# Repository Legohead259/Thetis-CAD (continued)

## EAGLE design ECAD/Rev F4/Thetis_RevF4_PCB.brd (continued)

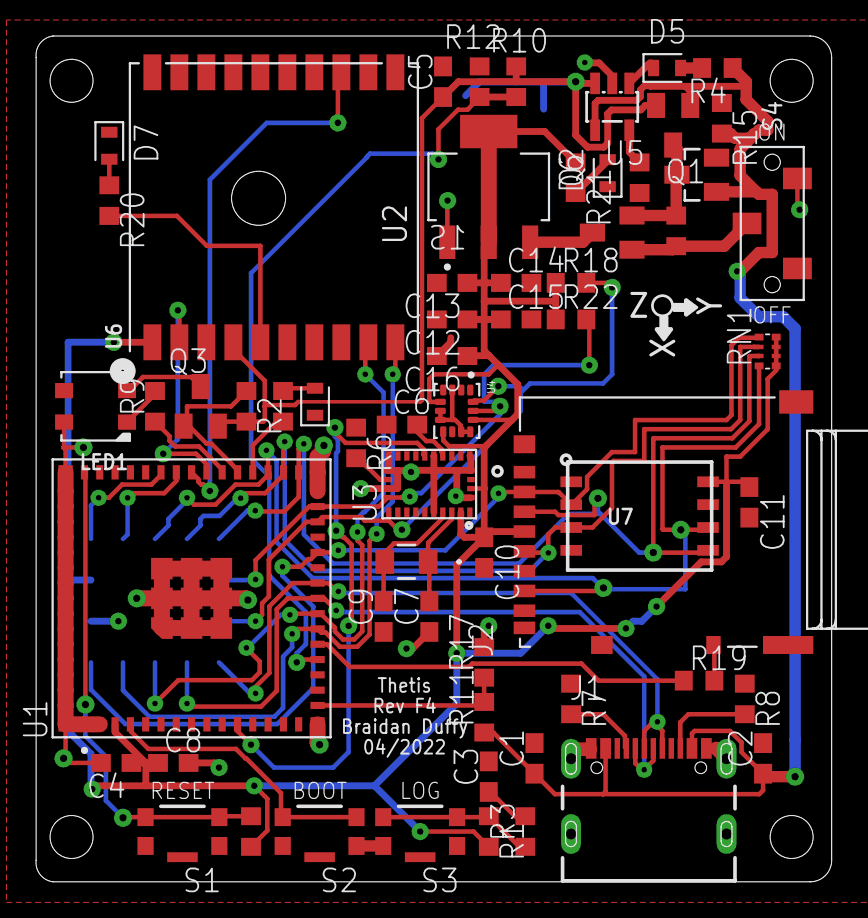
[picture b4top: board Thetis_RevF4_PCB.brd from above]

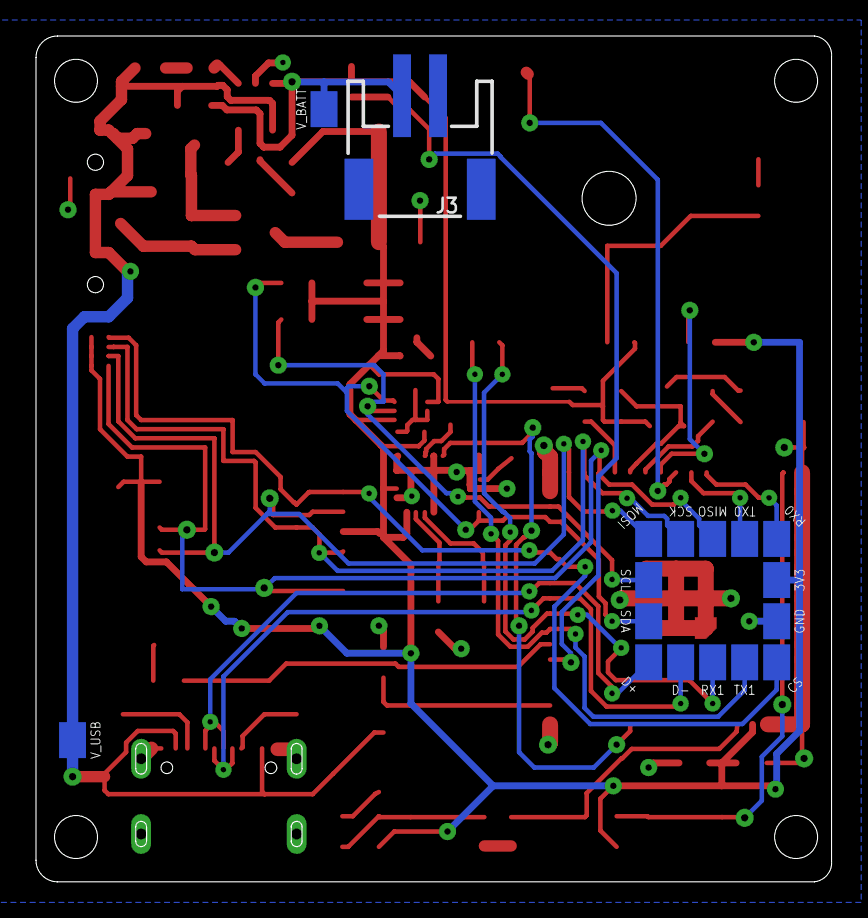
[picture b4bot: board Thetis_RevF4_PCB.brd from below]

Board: 2 copper layers, 44.2 x 47.0 mm, 79 parts (17 on the bottom side), 48 nets.

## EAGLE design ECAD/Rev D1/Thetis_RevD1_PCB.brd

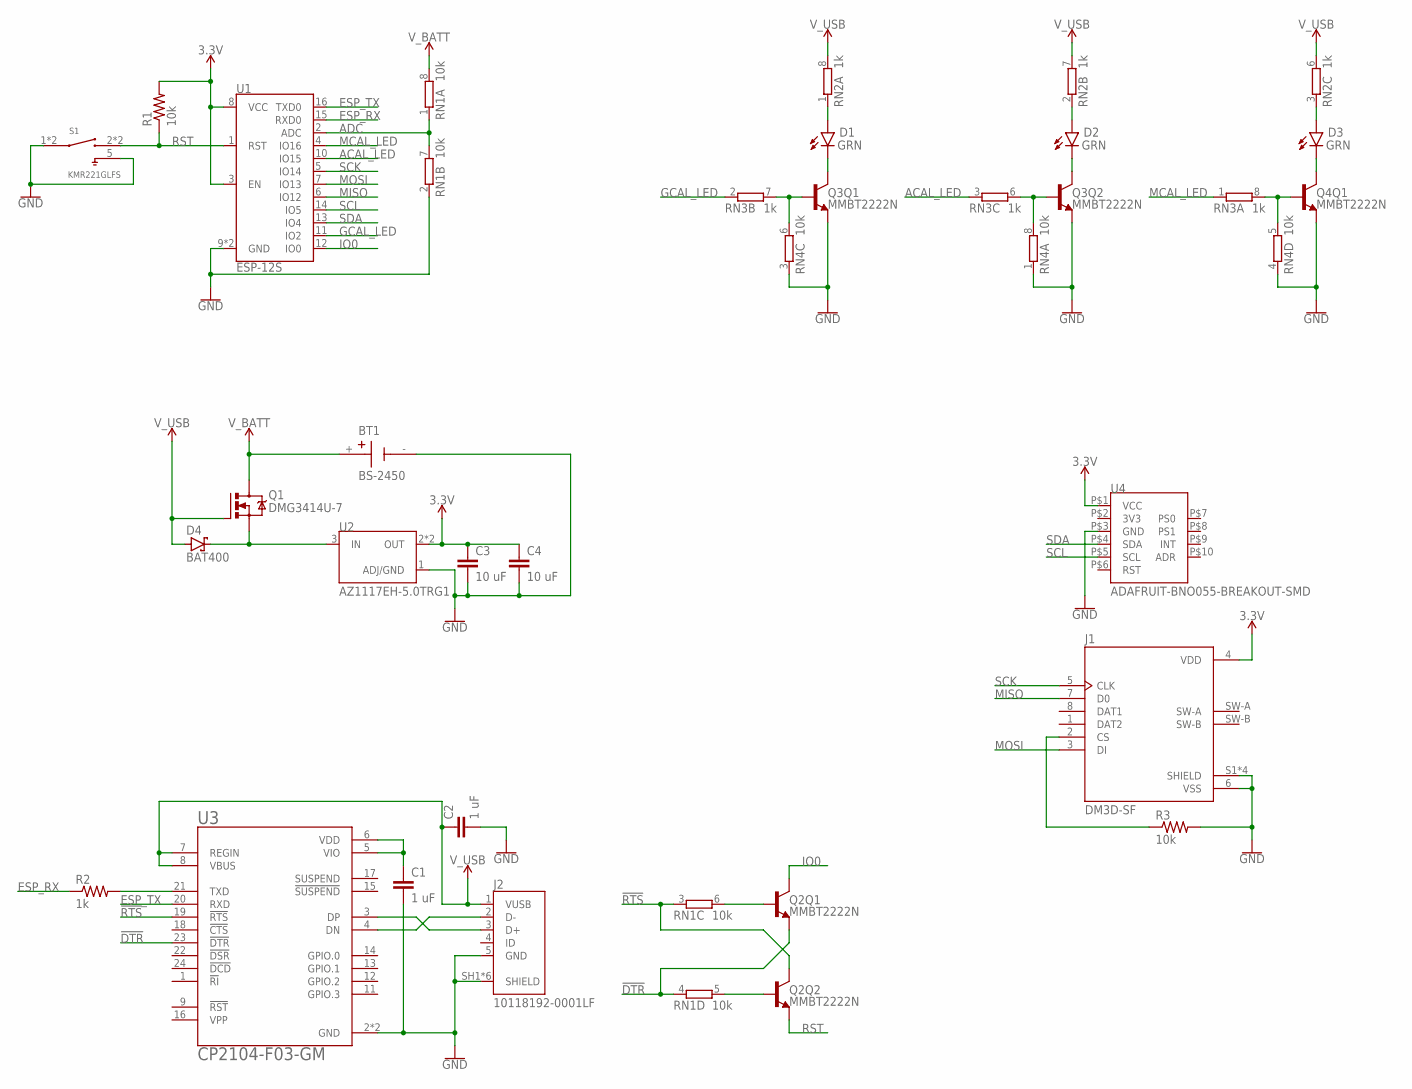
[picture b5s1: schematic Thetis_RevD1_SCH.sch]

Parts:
BT1: BS-2450; BAT_BS-2450
C1, C2: 1 uF; C0603
C3, C4: 10 uF; C0603
D1, D2, D3: GRN; LEDC1608X65N
D4: BAT400; SOT23
J1: DM3D-SF; HRS_DM3D-SF
J2: 10118192-0001LF; AMPHENOL_10118192-0001LF
Q1: DMG3414U-7; SOT23
Q2, Q3, Q4: MMBT2222N; SC70-6
R1, R3: 10k; R0603
R2: 1k; R0603
RN1, RN4: 10k; EXB28V
RN2, RN3: 1k; EXB28V
S1: KMR221GLFS; SW_KMR221GLFS
U1: ESP-12S
U2: AZ1117EH-5.0TRG1; SOT230P700X180-4N
U3: CP2104-F03-GM; QFN50P400X400X80-25N
U4: ADAFRUIT-BNO055-BREAKOUT-SMD

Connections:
3.3V: C3.1, C4.1, J1.4 (VDD), R1.2, U1.3 (EN), U1.8 (VCC), U2.2 (OUT), U2.4 (OUT), U4.P$1 (VCC)
3V3: U4.P$2 (3V3)
!DTR: Q2.4 (E), RN1.4 (1), U3.23 (!DTR)
!RTS: Q2.6 (C), RN1.3 (1), U3.19 (!RTS)
ACAL_LED: RN3.3 (1), U1.10 (IO15)
ADC: RN1.1, RN1.7 (2), U1.2 (ADC)
ESP_RX: R2.1, U1.15 (RXD0)
ESP_TX: U1.16 (TXD0), U3.20 (RXD)
GCAL_LED: RN3.2 (1), U1.11 (IO2)
GND: BT1.-, C1.2, C2.2, C3.2, C4.2, J1.6 (VSS), J1.S1 (SHIELD), J1.S2 (SHIELD), J1.S3 (SHIELD), J1.S4 (SHIELD), J2.5 (GND), J2.SH1 (SHIELD), J2.SH2 (SHIELD), J2.SH3 (SHIELD), J2.SH4 (SHIELD), J2.SH5 (SHIELD), J2.SH6 (SHIELD), Q3.1 (E), Q3.4 (E), Q4.4 (E), R3.2, RN1.2 (1), RN4.1, RN4.3 (1), RN4.4 (1), S1.1, S1.4 (1), S1.5, U1.9 (GND), U1.P$1 (GND), U2.1 (ADJ/GND), U3.2 (GND), U3.25 (GND), U4.P$3 (GND)
IO0: Q2.3 (C), U1.12 (IO0)
MCAL_LED: RN3.1, U1.4 (IO16)
MISO: J1.7 (D0), U1.6 (IO12)
MOSI: J1.3 (DI), U1.7 (IO13)
unnamed: J1.2 (CS), R3.1
unnamed: C1.1, U3.5 (VIO), U3.6 (VDD)
unnamed: R2.2, U3.21 (TXD)
unnamed: J2.3 (D+), U3.3 (DP)
unnamed: J2.2 (D-), U3.4 (DN)
unnamed: Q3.5 (B), RN3.7 (2), RN4.6 (2)
unnamed: Q2.2 (B), RN1.5 (2)
unnamed: D1.C, Q3.3 (C)
unnamed: Q2.5 (B), RN1.6 (2)
unnamed: D1.A, RN2.1
unnamed: D2.A, RN2.2 (1)
unnamed: D2.C, Q3.6 (C)
unnamed: D4.3 (C), Q1.2 (S), U2.3 (IN)
unnamed: Q3.2 (B), RN3.6 (2), RN4.8 (2)
unnamed: Q4.5 (B), RN3.8 (2), RN4.5 (2)
unnamed: D3.C, Q4.3 (C)
unnamed: D3.A, RN2.3 (1)
RST: Q2.1 (E), R1.1, S1.2 (3), S1.3, U1.1 (RST)
SCK: J1.5 (CLK), U1.5 (IO14)
SCL: U1.14 (IO5), U4.P$5 (SCL)
SDA: U1.13 (IO4), U4.P$4 (SDA)
V_BATT: BT1.+, Q1.3 (D), RN1.8 (2)
V_USB: C2.1, D4.1 (A), J2.1 (VUSB), Q1.1 (G), RN2.6 (2), RN2.7 (2), RN2.8 (2), U3.7 (REGIN), U3.8 (VBUS)

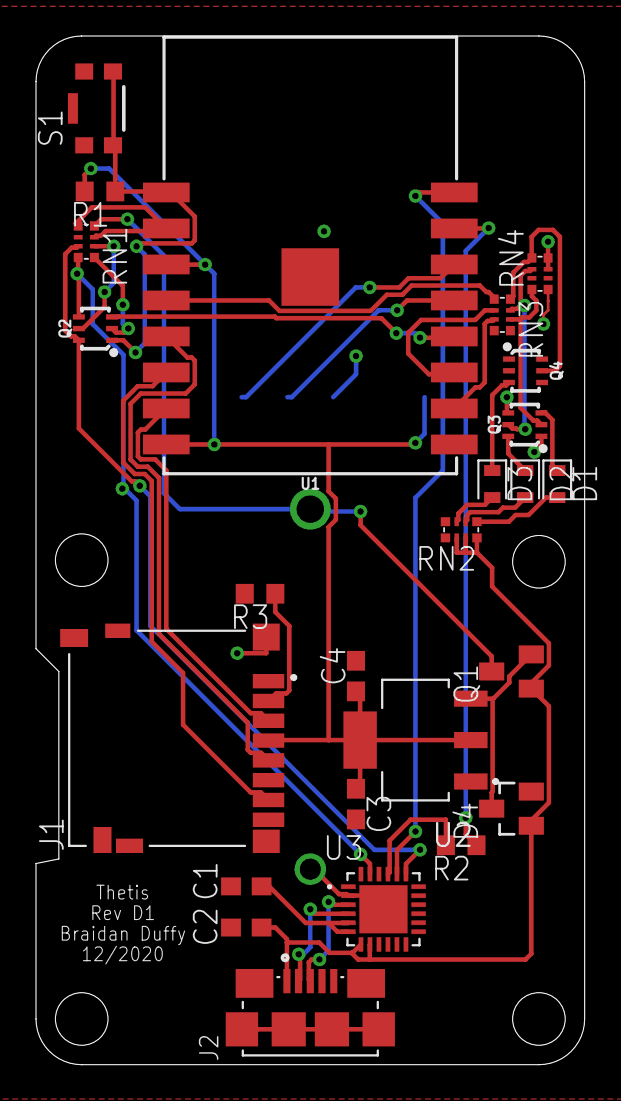
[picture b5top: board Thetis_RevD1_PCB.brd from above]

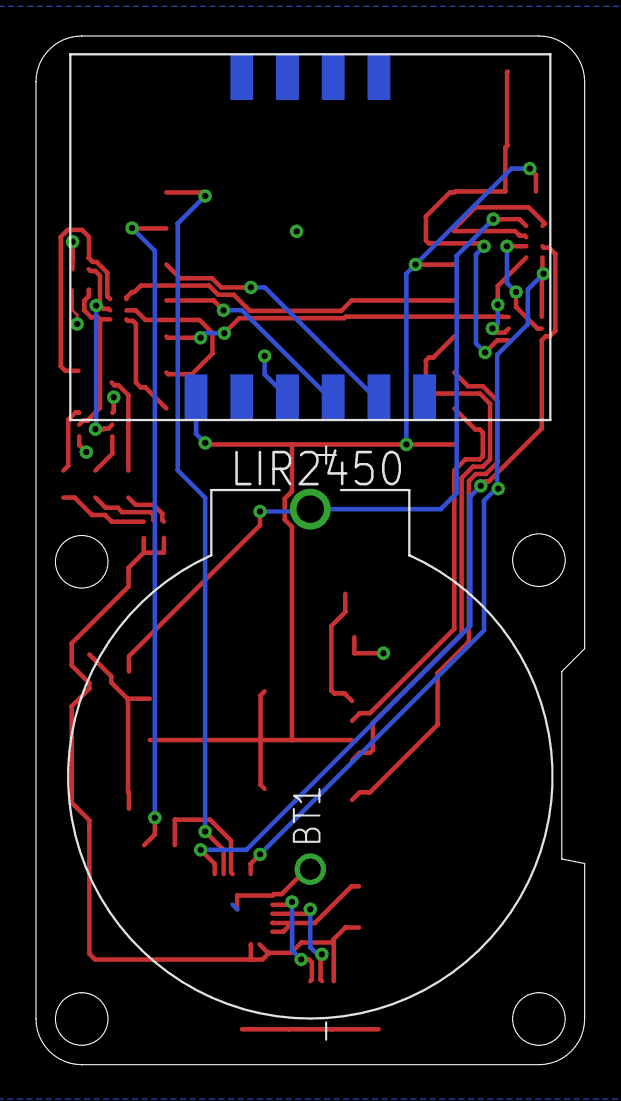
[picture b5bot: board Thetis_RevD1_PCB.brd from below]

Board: 2 copper layers, 30.5 x 57.1 mm, 27 parts (2 on the bottom side), 36 nets.

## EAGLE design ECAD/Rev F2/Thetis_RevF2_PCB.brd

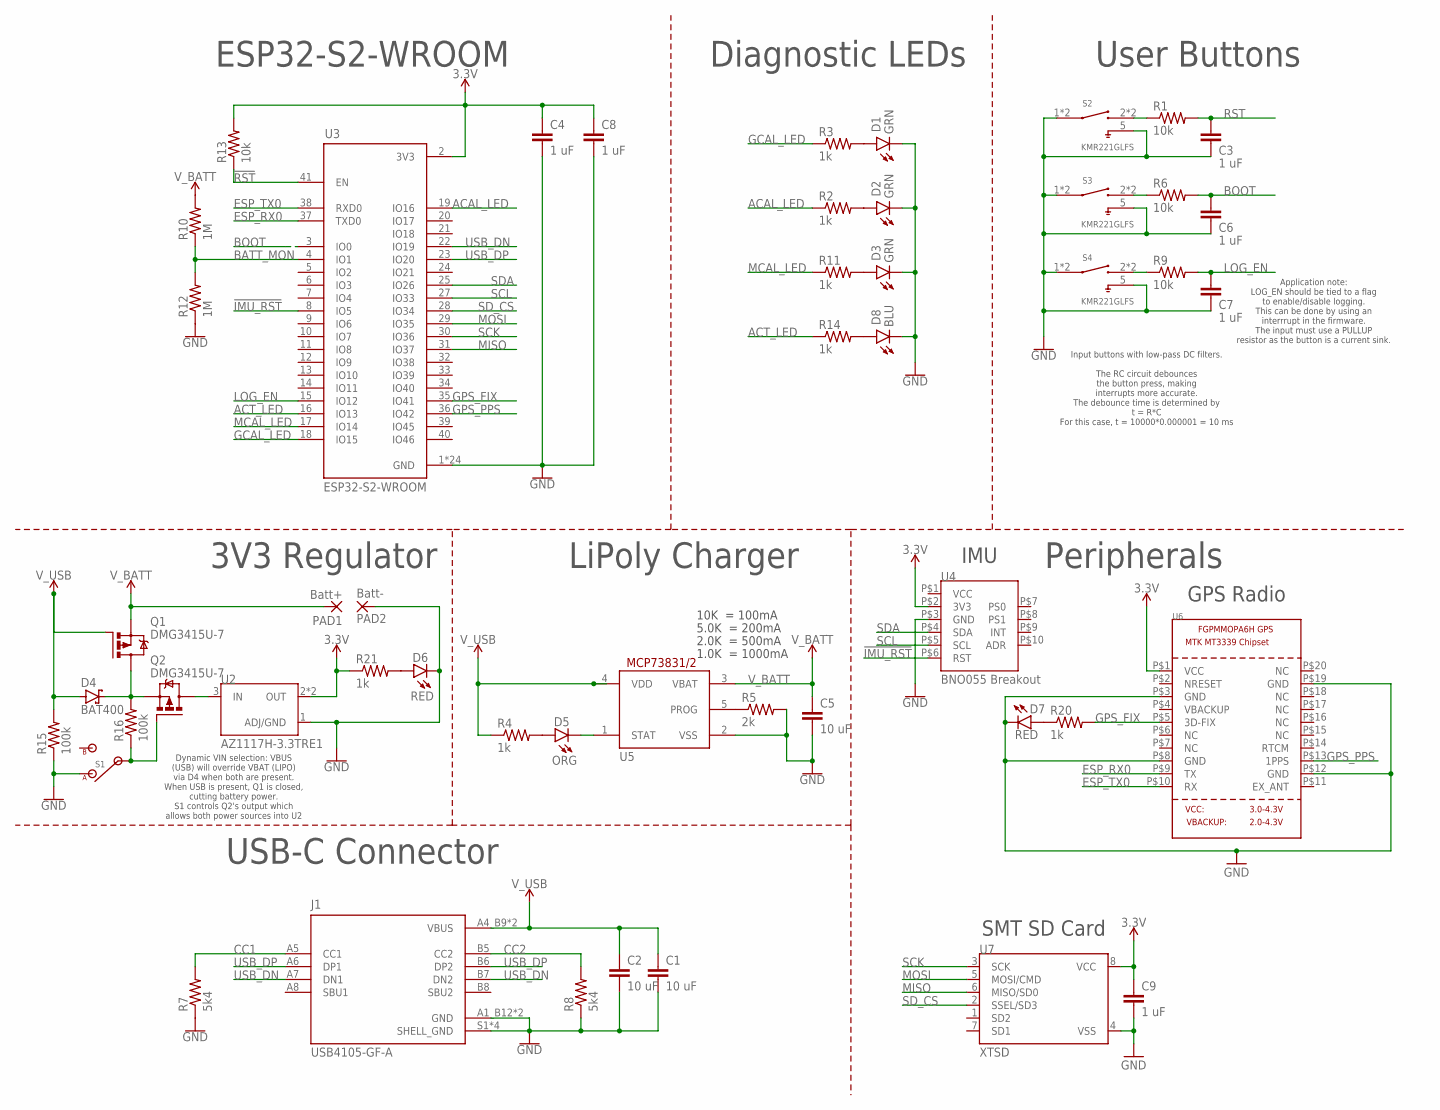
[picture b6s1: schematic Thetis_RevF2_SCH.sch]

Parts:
C1, C2, C5: 10 uF; C0603
C3, C4, C6, C7, C8, C9: 1 uF; C0603
D1, D2, D3: GRN; LEDC1608X65N
D4: BAT400; SOT23
D5: ORG; LEDC1608X65N
D6: RED; LEDC1608X65N
D7: RED; LEDC1608X35N
D8: BLU; LEDC1608X65N
J1: USB4105-GF-A; GCT_USB4105-GF-A
PAD1: Batt+; SMD2,54-5,08
PAD2: Batt-; SMD2,54-5,08
Q1, Q2: DMG3415U-7; SOT23
R1, R6, R9, R13: 10k; R0603
R2, R3, R4, R11, R14, R20, R21: 1k; R0603
R5: 2k; R0603
R7, R8: 5k4; R0603
R10, R12: 1M; R0603
R15, R16: 100k; R0603
S1: CL-SB-12X; CL-SB-12A
S2, S3, S4: KMR221GLFS; SW_KMR221GLFS
U2: AZ1117H-3.3TRE1; SOT230P700X180-4N
U3: ESP32-S2-WROOM; XCVR_ESP32-S2-WROOM
U4: BNO055 Breakout; ADAFRUIT-BNO055-BREAKOUT-SMD
U5: MCP73831/OT; SOT23-5L
U6: GPS_FGPMMOPA6H; FGPMMOPA6H
U7: XTSD; LGA8_8X6

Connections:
3.3V: C4.1, C8.1, C9.1, R13.2, R21.1, U2.2 (OUT), U2.4 (OUT), U3.2 (3V3), U4.P$2 (3V3), U6.P$1 (VCC), U7.8 (VCC)
!IMU_RST: U3.8 (IO5), U4.P$6 (RST)
!RST: R13.1, U3.41 (EN)
ACAL_LED: R2.1, U3.19 (IO16)
ACT_LED: R14.1, U3.16 (IO13)
BATT_MON: R10.1, R12.2, U3.4 (IO1)
BOOT: C6.1, R6.2, U3.3 (IO0)
CC1: J1.A5 (CC1), R7.2
CC2: J1.B5 (CC2), R8.2
ESP_RX0: U3.37 (TXD0), U6.P$9 (TX)
ESP_TX0: U3.38 (RXD0), U6.P$10 (RX)
GCAL_LED: R3.1, U3.18 (IO15)
GND: C1.2, C2.2, C3.2, C4.2, C5.2, C6.2, C7.2, C8.2, C9.2, D1.C, D2.C, D3.C, D6.C, D7.C, D8.C, J1.A1_B12 (GND), J1.B1_A12 (GND), J1.S1 (SHELL_GND), J1.S2 (SHELL_GND), J1.S3 (SHELL_GND), J1.S4 (SHELL_GND), PAD2.1, R5.2, R7.1, R8.1, R12.1, R15.1, S1.1, S2.1, S2.4 (1), S2.5, S3.1, S3.4 (1), S3.5, S4.1, S4.4 (1), S4.5, U2.1 (ADJ/GND), U3.1 (GND), U3.26 (GND), U3.42 (GND), U3.43.1 (GND), U3.43.2 (GND), U3.43.3 (GND), U3.43.4 (GND), U3.43.5 (GND), U3.43.6 (GND), U3.43.7 (GND), U3.43.8 (GND), U3.43.9 (GND), U3.43.10 (GND), U3.43.11 (GND), U3.43.12 (GND), U3.43.13 (GND), U3.43.14 (GND), U3.43.15 (GND), U3.43.16 (GND), U3.43.17 (GND), U3.43.18 (GND), U3.43.19 (GND), U3.43.20 (GND), U3.43.21 (GND), U4.P$3 (GND), U5.2 (VSS), U6.P$3 (GND), U6.P$8 (GND), U6.P$12 (GND), U6.P$19 (GND), U7.4 (VSS)
GPS_FIX: R20.2, U3.35 (IO41), U6.P$5 (3D-FIX)
GPS_PPS: U3.36 (IO42), U6.P$13 (1PPS)
LOG_EN: C7.1, R9.2, U3.15 (IO12)
MCAL_LED: R11.1, U3.17 (IO14)
MISO: U3.31 (IO37), U7.6 (MISO/SD0)
MOSI: U3.29 (IO35), U7.5 (MOSI/CMD)
unnamed: D7.A, R20.1
unnamed: D8.A, R14.2
unnamed: R1.1, S2.2 (3), S2.3
unnamed: Q2.3 (D), U2.3 (IN)
unnamed: R6.1, S3.2 (3), S3.3
unnamed: D1.A, R3.2
unnamed: Q2.1 (G), R16.1, S1.2
unnamed: R9.1, S4.2 (3), S4.3
unnamed: D2.A, R2.2
unnamed: D4.3 (C), Q1.3 (D), Q2.2 (S), R16.2
unnamed: D3.A, R11.2
unnamed: D5.A, R4.2
unnamed: D5.C, U5.1 (STAT)
unnamed: R5.1, U5.5 (PROG)
unnamed: D6.A, R21.2
RST: C3.1, R1.2
SCK: U3.30 (IO36), U7.3 (SCK)
SCL: U3.27 (IO33), U4.P$5 (SCL)
SDA: U3.25 (IO26), U4.P$4 (SDA)
SD_CS: U3.28 (IO34), U7.2 (SSEL/SD3)
USB_DN: J1.A7 (DN1), J1.B7 (DN2), U3.22 (IO19)
USB_DP: J1.A6 (DP1), J1.B6 (DP2), U3.23 (IO20)
VCC: U4.P$1 (VCC)
V_BATT: C5.1, PAD1.1, Q1.2 (S), R10.2, U5.3 (VBAT)
V_USB: C1.1, C2.1, D4.1 (A), J1.A4_B9 (VBUS), J1.B4_A9 (VBUS), Q1.1 (G), R4.1, R15.2, U5.4 (VDD)

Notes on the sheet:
10K = 100mA
5.0K = 200mA
2.0K = 500mA
1.0K = 1000mA
LiPoly Charger
3V3 Regulator
Peripherals
Diagnostic LEDs
ESP32-S2-WROOM
GPS Radio
Dynamic VIN selection: VBUS (USB) will override VBAT (LIPO) via D4 when both are present. When USB is present, Q1 is closed, cutting battery power. S1 controls Q2's output which allows both power sources into U2
IMU
SMT SD Card
USB-C Connector
Input buttons with low-pass DC filters. The RC circuit debounces the button press, making interrupts more accurate. The debounce time is determined by t = R*C For this case, t = 10000*0.000001 = 10 ms
User Buttons
Application note: LOG_EN should be tied to a flag to enable/disable logging. This can be done by using an interrrupt in the firmware. The input must use a PULLUP resistor as the button is a current sink.

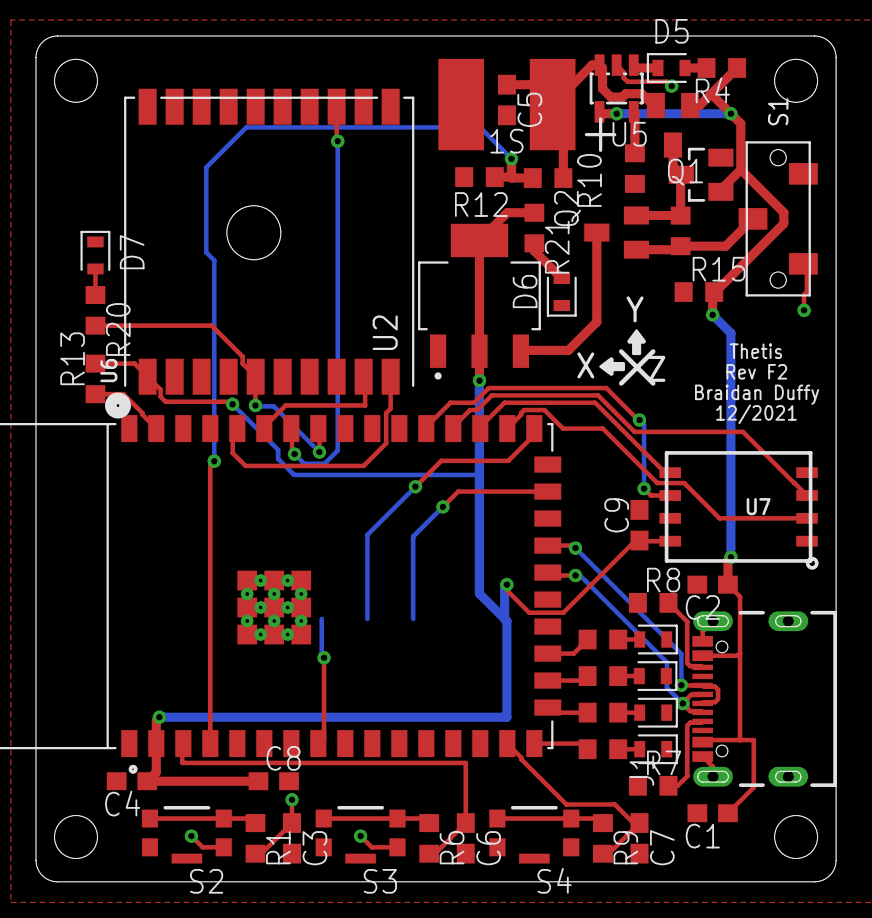
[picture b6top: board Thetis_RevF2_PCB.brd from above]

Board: 2 copper layers, 44.4 x 47.0 mm, 50 parts (1 on the bottom side), 43 nets.

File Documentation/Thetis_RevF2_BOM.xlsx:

Item | Manufactor Part Number | Supplier | Supplier Part Number | Name | Value | Package | Unit Price | Quantity | Total Price | Location | Datasheet | Notes
Battery Controller | MCP73831T-2ACI/OT | Digikey | MCP73831T-2ACI/OTCT-ND | U5 | 1S | SOT23-5 | 0.56000000000000005 | 1 | 0.56000000000000005 | https://www.digikey.com/en/products/detail/microchip-technol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 | http://www.microchip.com/mymicrochip/filehandler.aspx?ddocna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 | 1S LiPo
Button - Momentary | KMR221GLFS | Digikey | 401-1427-1-ND | S2, S3, S4 | SPST-NO | SMD | 0.49 | 3 | 1.47 | https://www.digikey.com/en/products/detail/c-k/KMR221GLFS/55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 | https://www.ckswitches.com/media/1479/kmr2.pdf | 0.05A 32V
Capacitor | 885012206026 | DigiKey | 732-7945-1-ND | C4, C8, C3, C6, C7, C9 | 1 uF | 0603 | 0.23 | 6 | 1.3800000000000001 | https://www.digikey.com/product-detail/en/wurth-electronics-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 | https://katalog.we-online.de/pbs/datasheet/885012206026.pdf | 10V X7R
Capacitor | ZRB18AR61E106ME01L | Digikey | 490-10991-1-ND | C1, C2, C5 | 10 uF | 0603 | 0.35599999999999998 | 3 | 1.0680000000000001 | https://www.digikey.com/product-detail/en/murata-electronics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 | https://search.murata.co.jp/Ceramy/image/img/A01X/G101/ENG/Z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 | 25V X5R
Connector - USB-C | USB4105-GF-A | DigiKey | 2073-USB4105-GF-ATR-ND | J1 |  | SMD | 0.72 | 1 | 0.72 | https://www.digikey.com/en/products/detail/USB4105-GF-A/2073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 | https://gct.co/files/specs/usb4105-spec.pdf | USB2.0, USB-C receptacle
Diode - Schottky | BAT400D-7-F | Digikey | BAT400D-FDICT-ND | D4 |  | SOT23-3 | 0.45 | 1 | 0.45 | https://www.digikey.com/product-detail/en/diodes-incorporate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 | https://www.diodes.com/assets/Datasheets/ds30182.pdf | 40V, 500mA
IMU | BNO055 | Adafruit | 2472 | U4 |  | SMT | 34.950000000000003 | 1 | 34.950000000000003 | https://www.adafruit.com/product/2472 | https://learn.adafruit.com/adafruit-bno055-absolute-orientat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 | Breakout board soldered to back of PCB
LED | SML-D12P8WT86C | DigiKey | SML-D12P8WT86CCT-ND | D1, D2, D3 | GRN | 0603 | 0.48 | 3 | 1.44 | https://www.digikey.com/product-detail/en/rohm-semiconductor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 | https://www.rohm.com/datasheet/SML-D12P8W(C)/sml-d12x8(c)-e | 2.2Vf
LED | 150060BS55040 | Digikey | 732-12013-1-ND | D8 | BLU | 0603 | 0.17 | 1 | 0.17 | https://www.digikey.com/product-detail/en/wurth-electronics-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 | https://katalog.we-online.de/pbs/datasheet/150060BS55040.pdf | 3.2Vf
LED | SML-D12U1WT86 | Digikey | SML-D12U1WT86CT-ND | D6, D7 | RED | 0603 | 0.16200000000000001 | 2 | 0.32400000000000001 | https://www.digikey.com/product-detail/en/rohm-semiconductor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 | https://www.rohm.com/datasheet/SML-D12U1W | 2.2Vf
LED | ASMT-RA45-AP932 | Digikey | 516-3217-1-ND | D5 | AMB | 0603 | 0.33300000000000002 | 1 | 0.33300000000000002 | https://www.digikey.com/product-detail/en/broadcom-limited/A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 | https://docs.broadcom.com/docs/AV02-0378EN | 2Vf
Microcontroller | ESP32-S2-WROOM | DigiKey | 1965-ESP32-S2-WROOMCT-ND | U3 |  | SMT | 2.13 | 1 | 2.13 | https://www.digikey.com/en/products/detail/espressif-systems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 | https://www.espressif.com/sites/default/files/documentation/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
MOSFET - P-Channel | AOSS21311C | DigiKey | 785-AOSS21311CCT-ND | Q1, Q2 |  | SOT-23-3 | 0.36199999999999999 | 2 | 0.72399999999999998 | https://www.digikey.com/en/products/detail/AOSS21311C/785-AO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 | http://aosmd.com/res/data_sheets/AOSS21311C.pdf | Vgs = -1.7V, 30V, 4.3A
Radio - GPS | PA6H | Adafruit | 790 | U6 |  | SMT | 29.95 | 1 | 29.95 | https://www.adafruit.com/product/790 |  | MTK3339 GPS
Regulator - LDO | AZ1117H-3.3TRE1 | Digikey | AZ1117H-3.3TRE1DICT-ND | U2 | 3V3 | SOT223 | 0.51 | 1 | 0.51 | https://www.digikey.com/en/products/detail/diodes-incorporat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 | https://media.digikey.com/pdf/Data%20Sheets/Diodes%20PDFs/AZ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 | LDO 1A max
Resistor | RNCP0603FTD10K0 | DigiKey | RNCP0603FTD10K0CT-ND | R13, R1, R6, R7 | 10 kΩ | 0603 | 2.7300000000000001E-2 | 4 | 0.10920000000000001 | https://www.digikey.com/product-detail/en/stackpole-electron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 | https://www.seielect.com/catalog/sei-rncp.pdf | 0.125W
Resistor | CRCW06031M00FKEAC | DigiKey | 541-5248-1-ND | R10, R12 | 1M | 0603 | 0.1 | 2 | 0.2 | https://www.digikey.com/en/products/detail/vishay-dale/CRCW0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 | https://www.vishay.com/docs/28773/crcwce3.pdf | 0.1W
Resistor | ESR03EZPJ102 | Digikey | RHM1.0KDCT-ND | R2, R3, R4, R11, R14, R20, R21 | 1 kΩ | 0603 | 8.3000000000000004E-2 | 7 | 0.58100000000000007 | https://www.digikey.com/product-detail/en/rohm-semiconductor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 | https://www.rohm.com/datasheet/ESR01MZPF/esr-e | 0.25W
Resistor | RC0603FR-07100KL | Digikey | 311-100KHRCT-ND | R15, R16 | 100kΩ | 0603 | 0.1 | 2 | 0.2 | https://www.digikey.com/en/products/detail/yageo/RC0603FR-07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 | https://www.yageo.com/upload/media/product/productsearch/dat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 | 0.1W
Resistor | ERJ-3GEYJ202V | Digikey | P2.0KGCT-ND | R5 | 2 kΩ | 0603 | 4.2999999999999997E-2 | 1 | 4.2999999999999997E-2 | https://www.digikey.com/product-detail/en/panasonic-electron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 | http://industrial.panasonic.com/www-cgi/jvcr13pz.cgi?E+PZ+3+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 | 0.1W
Resistor | MCT06030C5101FP500 | Digikey | 749-1663-1-ND | R7, R8 | 5.1 kΩ | 0603 | 0.152 | 2 | 0.30399999999999999 | https://www.digikey.com/product-detail/en/vishay-beyschlag/M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 | http://www.vishay.com/docs/28705/mcx0x0xpro.pdf | 0.125W
Storage - NAND Flash | XTSD08GLGEAG | LCSC | C558840 | U7 | 1 GB | SMT | 11.58 | 1 | 11.58 | https://lcsc.com/product-detail/NAND-FLASH_XTX-XTSD08GLGEAG_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 | https://datasheet.lcsc.com/lcsc/2005251034_XTX-XTSD08GLGEAG_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 | 1 GB, treat as SD card in SW
Total |  |  |  |  |  |  |  | 47 | 89.196200000000019

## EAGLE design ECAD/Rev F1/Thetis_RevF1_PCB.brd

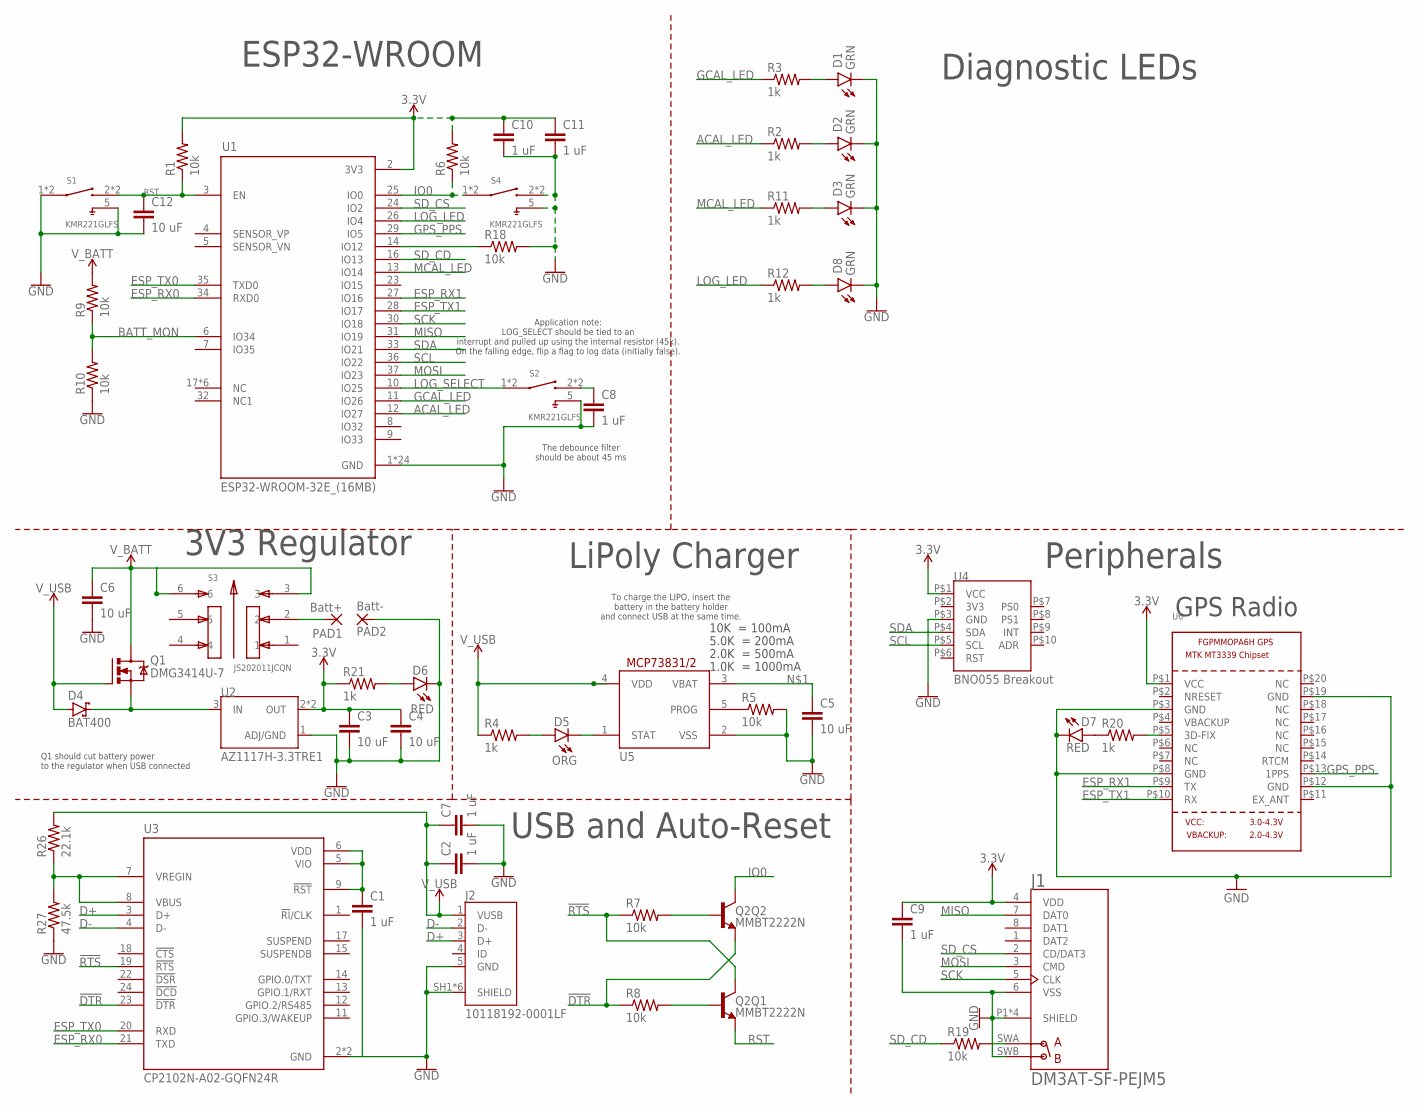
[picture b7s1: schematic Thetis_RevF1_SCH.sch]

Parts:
C1, C2, C7, C8, C9, C10, C11: 1 uF; C0603
C3, C4, C5, C6, C12: 10 uF; C0603
D1, D2, D3, D8: GRN; LEDC1608X65N
D4: BAT400; SOT23
D5: ORG; LEDC1608X65N
D6: RED; LEDC1608X65N
D7: RED; LEDC1608X35N
J1: DM3AT-SF-PEJM5; HRS_DM3AT-SF-PEJM5
J2: 10118192-0001LF; AMPHENOL_10118192-0001LF
PAD1: Batt+; SMD2,54-5,08
PAD2: Batt-; SMD2,54-5,08
Q1: DMG3414U-7; SOT23
Q2: MMBT2222N; SC70-6
R1, R5, R6, R7, R8, R9, R10, R18, R19: 10k; R0603
R2, R3, R4, R11, R12, R20, R21: 1k; R0603
R26: 22.1k; R0603
R27: 47.5k; R0603
S1, S2, S4: KMR221GLFS; SW_KMR221GLFS
S3: JS202011JCQN; SW_JS202011JCQN
U1: ESP32-WROOM-32E_(16MB); MODULE_ESP32-WROOM-32E_(16MB)
U2: AZ1117H-3.3TRE1; SOT230P700X180-4N
U3: CP2102N-A02-GQFN24R; QFN50P400X400X80-25N
U4: BNO055 Breakout; ADAFRUIT-BNO055-BREAKOUT-SMD
U5: MCP73831/OT; SOT23-5L
U6: GPS_FGPMMOPA6H; FGPMMOPA6H

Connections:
3.3V: C3.1, C4.1, C9.1, C10.1, C11.1, J1.4 (VDD), R1.2, R6.2, R21.1, U1.2 (3V3), U2.2 (OUT), U2.4 (OUT), U4.P$1 (VCC), U6.P$1 (VCC)
3V3: U4.P$2 (3V3)
!DTR: Q2.1 (E), R8.1, U3.23 (!DTR)
!RTS: Q2.3 (C), R7.1, U3.19 (!RTS)
ACAL_LED: R2.1, U1.12 (IO27)
BATT_MON: R9.1, R10.2, U1.6 (IO34)
D+: J2.3 (D+), U3.3 (D+)
D-: J2.2 (D-), U3.4 (D-)
ESP_RX0: U1.34 (RXD0), U3.21 (TXD)
ESP_RX1: U1.27 (IO16), U6.P$9 (TX)
ESP_TX0: U1.35 (TXD0), U3.20 (RXD)
ESP_TX1: U1.28 (IO17), U6.P$10 (RX)
GCAL_LED: R3.1, U1.11 (IO26)
GND: C1.2, C2.2, C3.2, C4.2, C5.2, C6.2, C7.2, C8.2, C9.2, C10.2, C11.2, C12.2, D1.C, D2.C, D3.C, D6.C, D7.C, D8.C, J1.6 (VSS), J1.P1 (SHIELD), J1.P2 (SHIELD), J1.P3 (SHIELD), J1.P4 (SHIELD), J1.SWB (B), J2.5 (GND), J2.SH1 (SHIELD), J2.SH2 (SHIELD), J2.SH3 (SHIELD), J2.SH4 (SHIELD), J2.SH5 (SHIELD), J2.SH6 (SHIELD), PAD2.1, R5.2, R10.1, R18.2, R27.1, S1.1, S1.4 (1), S1.5, S2.5, S4.2 (3), S4.3, S4.5, U1.1 (GND), U1.15 (GND), U1.38 (GND), U1.39_1 (GND), U1.39_2 (GND), U1.39_3 (GND), U1.39_4 (GND), U1.39_5 (GND), U1.39_6 (GND), U1.39_7 (GND), U1.39_8 (GND), U1.39_9 (GND), U1.39_10 (GND), U1.39_11 (GND), U1.39_12 (GND), U1.39_13 (GND), U1.39_14 (GND), U1.39_15 (GND), U1.39_16 (GND), U1.39_17 (GND), U1.39_18 (GND), U1.39_19 (GND), U1.39_20 (GND), U1.39_21 (GND), U2.1 (ADJ/GND), U3.2 (GND), U3.25 (GND), U4.P$3 (GND), U5.2 (VSS), U6.P$3 (GND), U6.P$8 (GND), U6.P$12 (GND), U6.P$19 (GND)
GPS_PPS: U1.29 (IO5), U6.P$13 (1PPS)
IO0: Q2.6 (C), R6.1, S4.1, S4.4 (1), U1.25 (IO0)
LOG_LED: R12.1, U1.26 (IO4)
LOG_SELECT: S2.1, S2.4 (1), U1.10 (IO25)
MCAL_LED: R11.1, U1.13 (IO14)
MISO: J1.7 (DAT0), U1.31 (IO19)
MOSI: J1.3 (CMD), U1.37 (IO23)
unnamed: C5.1, PAD1.1, S3.2, U5.3 (VBAT)
unnamed: D7.A, R20.1
unnamed: R20.2, U6.P$5 (3D-FIX)
unnamed: R18.1, U1.14 (IO12)
unnamed: Q2.5 (B), R8.2
unnamed: D1.A, R3.2
unnamed: Q2.2 (B), R7.2
unnamed: C8.1, S2.2 (3), S2.3
unnamed: D2.A, R2.2
unnamed: D4.3 (C), Q1.2 (S), U2.3 (IN)
unnamed: D3.A, R11.2
unnamed: D8.A, R12.2
unnamed: C1.1, U3.5 (VIO), U3.6 (VDD), U3.9 (!RST)
unnamed: R26.1, R27.2, U3.7 (VREGIN), U3.8 (VBUS)
unnamed: D5.A, R4.2
unnamed: D5.C, U5.1 (STAT)
unnamed: R5.1, U5.5 (PROG)
unnamed: J1.SWA (A), R19.2
unnamed: D6.A, R21.2
RST: C12.1, Q2.4 (E), R1.1, S1.2 (3), S1.3, U1.3 (EN)
SCK: J1.5 (CLK), U1.30 (IO18)
SCL: U1.36 (IO22), U4.P$5 (SCL)
SDA: U1.33 (IO21), U4.P$4 (SDA)
SD_CD: R19.1, U1.16 (IO13)
SD_CS: J1.2 (CD/DAT3), U1.24 (IO2)
V_BATT: C6.1, Q1.3 (D), R9.2, S3.3, S3.6
V_USB: C2.1, C7.1, D4.1 (A), J2.1 (VUSB), Q1.1 (G), R4.1, R26.2, U5.4 (VDD)

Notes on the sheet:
10K = 100mA
5.0K = 200mA
2.0K = 500mA
1.0K = 1000mA
To charge the LIPO, insert the battery in the battery holder and connect USB at the same time.
LiPoly Charger
USB and Auto-Reset
3V3 Regulator
Q1 should cut battery power to the regulator when USB connected
Peripherals
Diagnostic LEDs
ESP32-WROOM
GPS Radio
Application note: LOG_SELECT should be tied to an interrupt and pulled up using the internal resistor (45k). On the falling edge, flip a flag to log data (initially false).
The debounce filter should be about 45 ms

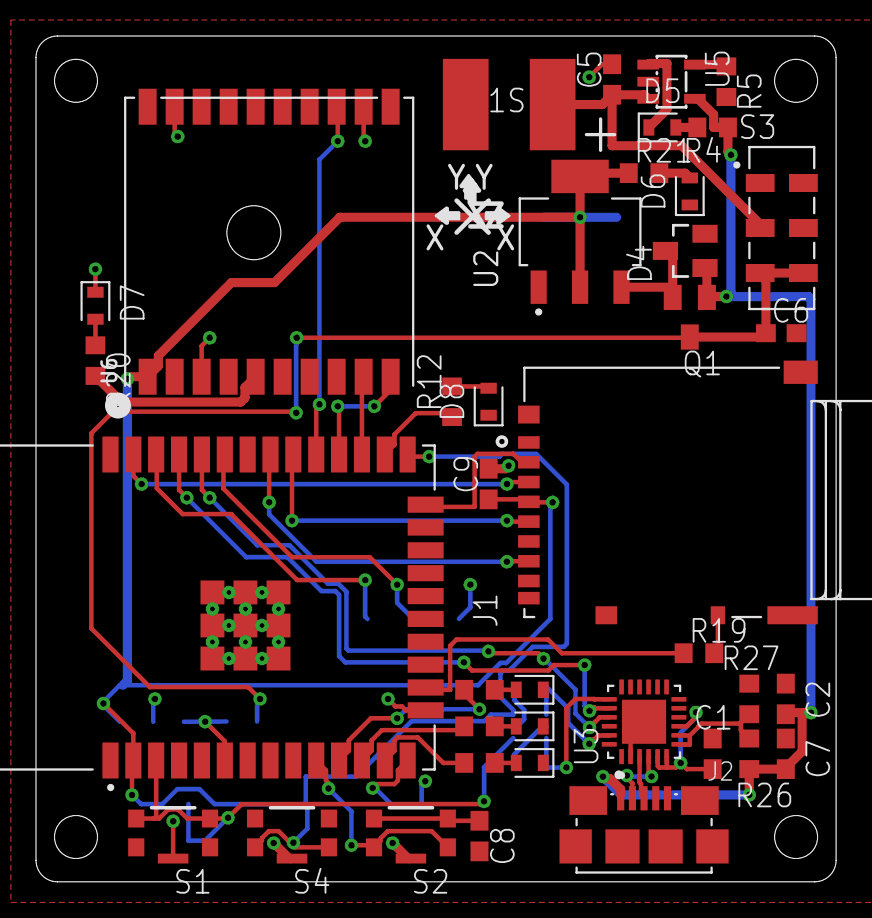
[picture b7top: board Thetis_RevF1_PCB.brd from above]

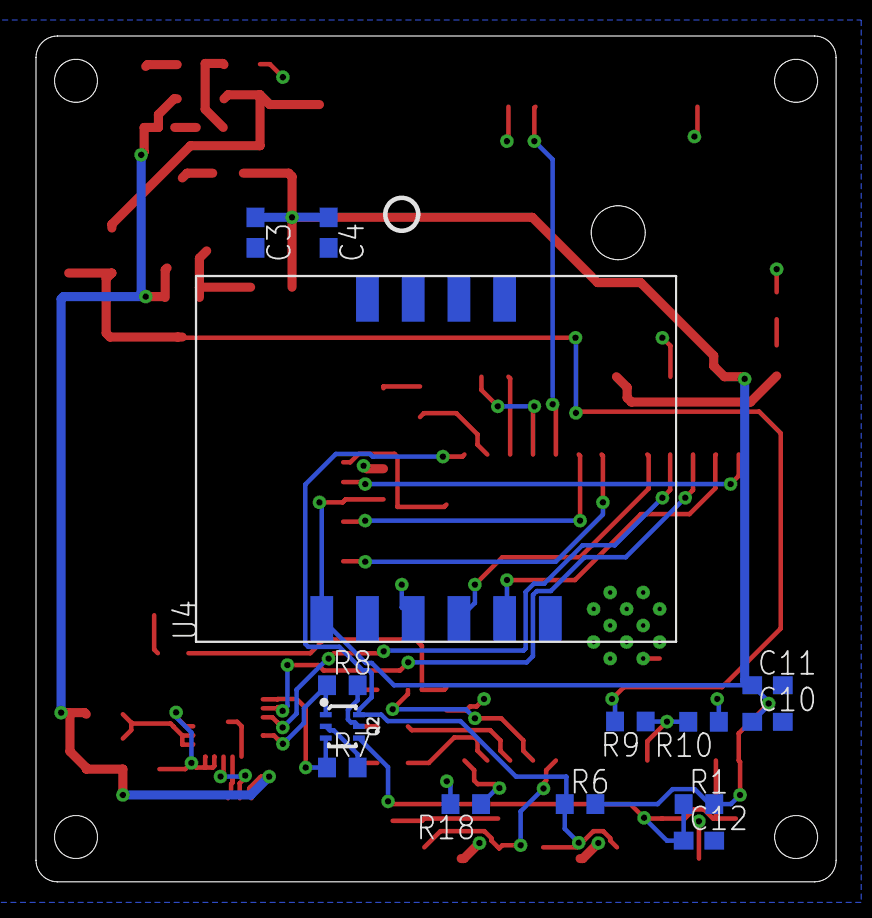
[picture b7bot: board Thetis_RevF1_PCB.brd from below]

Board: 2 copper layers, 44.5 x 47.0 mm, 54 parts (14 on the bottom side), 47 nets.

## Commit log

2022-02-04 Initial Commit Added CAD files and documentation
2022-03-25 Added Rev F3 Schematic
2022-07-14 Added RevF4 Schematics
2022-07-14 Added RevF4 source files
2022-10-26 Added some deployment data, changed nomenclature
2022-10-26 Restructured documentation to make it a bit easier to navigate
2022-10-26 Added Rev G1
2022-10-26 Added Rev F4 gerber files
2022-10-26 Updated gitignore
2022-10-26 Updated documentation files
2023-01-11 Update refresh
2023-10-24 Added new schematic and board files
2023-10-24 Added Revision F5 F360 archive
2023-10-26 Added ECAD files Added BOMs for all boards Added F360 archives Added Gerber for RevF6
2023-10-26 Added PDFs of schematics
